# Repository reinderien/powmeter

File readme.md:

Introduction
============

What is this?
-------------

This is the next project in a series to teach electronics to members of 
[KwartzLab](https://www.kwartzlab.ca/)
(and the public, by association).

It is a power meter meant to exercise knowledge of Arduino and intermediate 
electronics, as voted by the membership.

What will it do?
----------------

This will measure current - and calculate power, and estimated cost - of 
electricity going through a household single-phase 120Vac mains plug. This is
useful for a number of reasons, not limited to:

- Knowing which appliances are more or less efficient
- Learning how to be more environmentally conscious
- Knowing if an appliance is really off when it says it's off

Design notes
============

Current transformer
-------------------

First, we choose a current-sensing strategy. Our strategy will be
"non-intrusive":

- Offer a female 120V polarized, grounded plug for the appliance to plug into
- On the inside of the meter, run live (possibly with multiple turns) through
  the air core of a current transformer coil, without a physical connection
- On the other side, connect the mains wires to a male 120V polarized plug

The current transformer coil will be physically connected to the rest of the
isolation and sensing circuit. Even though there is not a physical connection 
between the mains wire and the rest of the circuit, a small amount of energy
will be transferred through the principle of electromagnetic induction. This
is the same principle that allows electric motors and power transformers to
work.

Since it's easy, let's look in the
[Digikey Current Sense Transformers](https://www.digikey.ca/products/en/transformers/current-sense-transformers/163)
section, with these criteria:

- Part Status = Active
- In Stock
- View prices at quantity 10
- Type: Non-invasive (either split or solid core is fine)
- Frequency range - anything whose minimum frequency is at or below 60 Hz. This
  is the frequency of alternating current (AC) mains voltage in North America.

This narrows our options considerably. Let's choose the least expensive part
that meets these criteria, the
[ASM-010](https://talema.com/uploads/documents/product-datasheets/ASM%20Series.pdf).

It operates as the secondary coil of a transformer, where the primary "coil" is
the sensed wire. In a normal transformer, the primary and secondary coils have
a different number of windings and are not electrically connected, and are used
for the purposes of voltage step-up/down and current step-down/up. Here, this 
is technically a step-up transformer because the number of windings from the
primary to secondary coil goes way up (the primary only has one winding, or
maybe two if we can squeeze in another wire). But a voltage step-up transformer
is a current step-down transformer, and this is what we use it for. We use it
to step down the current from whatever is going through the mains line.

Other characteristics of this part:

- It is through-hole, so it is easy to prototype
- The primary-to-secondary isolation rating is at least 2500 volts. This is
  called
  [galvanic isolation](https://en.wikipedia.org/wiki/Galvanic_isolation) and is
  a critical safety measure in high-voltage circuits.
- It can fit a mains wire up to 5mm in diameter
- It can inductively couple to 50-60Hz mains
- It has an accuracy tolerance of ±10% in the output voltage
- It is rated to a maximum of 10 amps AC
- They recommend that, to convert the output current into voltage, a 50Ω load
  resistor be added

Looking at the spreadsheet, the most important graph is the Typical Response.
For the ASM-010, the sensitivity is:

    30mV
    ---- ~ 3.33 mΩ
    9A 

This sensitivity, 3.33 mΩ, can also be thought of as the
[transresistance](https://en.wikipedia.org/wiki/Transconductance#Transresistance)
of the transformer. Transresistance is a ratio of voltage output change to
current input change. It's more conveniently expressed as 1/3.33 mΩ ~ 300℧ (300
mho, the unit of conductance which is the reciprocal of resistance).

In the case where the primary has a single winding and the recommended 50Ω load
is used, if the input is 10A and the output is 33.3mV, then the output current is

    33.3mV
    ---- = 667μA
    50Ω

In this case, at the top of the range, only 667 micro-amps (0.000667 A) are
being output from the transformer. At the other end of the range, we would
expect to see devices like a phone charger at partial load draw much less than
this. The minimum resolvable current is dictated by the resolution of our
analog-to-digital converter (ADC) as well as our gain. If we use the
[Arduino Uno rev 3](https://store.arduino.cc/usa/arduino-uno-rev3) with an
[ATmega328P microcontroller](http://ww1.microchip.com/downloads/en/DeviceDoc/Atmel-7810-Automotive-Microcontrollers-ATmega328P_Datasheet.pdf),
then it is a 10-bit ADC:

    Resolution = 2^10 = 1024
    Vout min = 33.3mV / 1024 ~ 32.6μV
    Vin min = 32.6μV * 300℧ ~ 9.77mA

In other words, the minimum resolvable current for the Arduino would be one
where the ADC reads "1" out of a possible 1023. With a rectifier/amplifier that
amplifies 33.3mVac to 5V peak, this would be read for a transformer output voltage of
32.6μV, which would be produced by a current of 9.77mA AC through the primary.

This in turn means that, if we only have a single gain, our minimum resolvable
power is

    P = 120V * 9.77mA = 1.17W

To find out how much this costs: of Mar 30, 2020, Waterloo North Hydro's
rates disregarding COVID-19 discounts are:

- $0.101/kWh off-peak, 12 hours/day weekdays, 24 hours/day weekends
- $0.144/kWh mid-peak, 6 hours/day weekdays
- $0.208/kWh on-peak, 6 hours/day weekdays

An amortized monthly rate is then

    4*[5*(12*0.101 + 6*0.144 + 6*0.208) + 2*24*0.101]/1000 = $0.085872/W/month

Over one month, the cost of 1.17W is then

    1.17W * $0.085872 = $0.10

So our single-gain system has a resolution of ten cents per month. We could add
a second amplifier to get better resolution for low-power devices but that does
not seem worth it.

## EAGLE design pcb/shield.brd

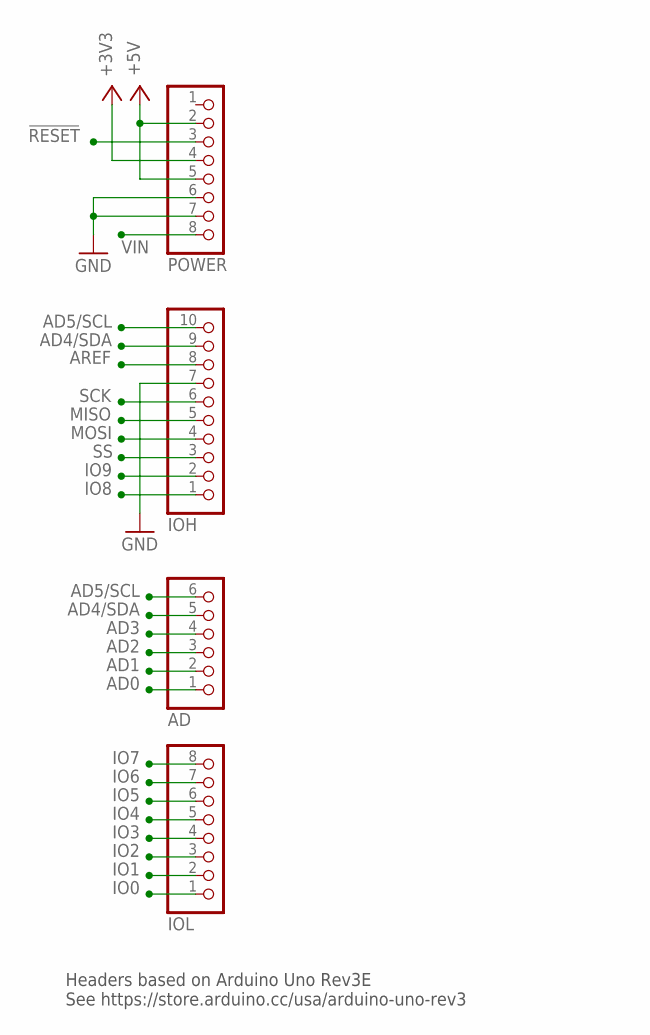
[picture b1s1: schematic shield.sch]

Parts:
AD: 6x1F-H8.5; 1X06
IOH: 10x1F-H8.5; 1X10
IOL: 8x1F-H8.5; 1X08
POWER: 8x1F-H8.5; 1X08

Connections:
!RESET: POWER.3
+3V3: POWER.4
+5V: POWER.2, POWER.5
AD0: AD.1
AD1: AD.2
AD2: AD.3
AD3: AD.4
AD4/SDA: AD.5, IOH.9
AD5/SCL: AD.6, IOH.10
AREF: IOH.8
GND: IOH.7, POWER.6, POWER.7
IO0: IOL.1
IO1: IOL.2
IO2: IOL.3
IO3: IOL.4
IO4: IOL.5
IO5: IOL.6
IO6: IOL.7
IO7: IOL.8
IO8: IOH.1
IO9: IOH.2
MISO: IOH.5
MOSI: IOH.4
SCK: IOH.6
SS: IOH.3
VIN: POWER.8

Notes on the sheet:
Headers based on Arduino Uno Rev3E See https://store.arduino.cc/usa/arduino-uno-rev3

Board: 2 copper layers, 4 parts (0 on the bottom side), 4 nets, no tracks yet.

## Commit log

2020-04-01 Initial, empty content
2020-04-01 Some initial analysis
2020-04-02 New sim for fully-rectified superdiode amp
2020-04-06 Eagle files for Arduino
2020-04-06 Ignore eagle temp files
2020-04-06 Initial shield headers
2020-04-07 2.5V ref
